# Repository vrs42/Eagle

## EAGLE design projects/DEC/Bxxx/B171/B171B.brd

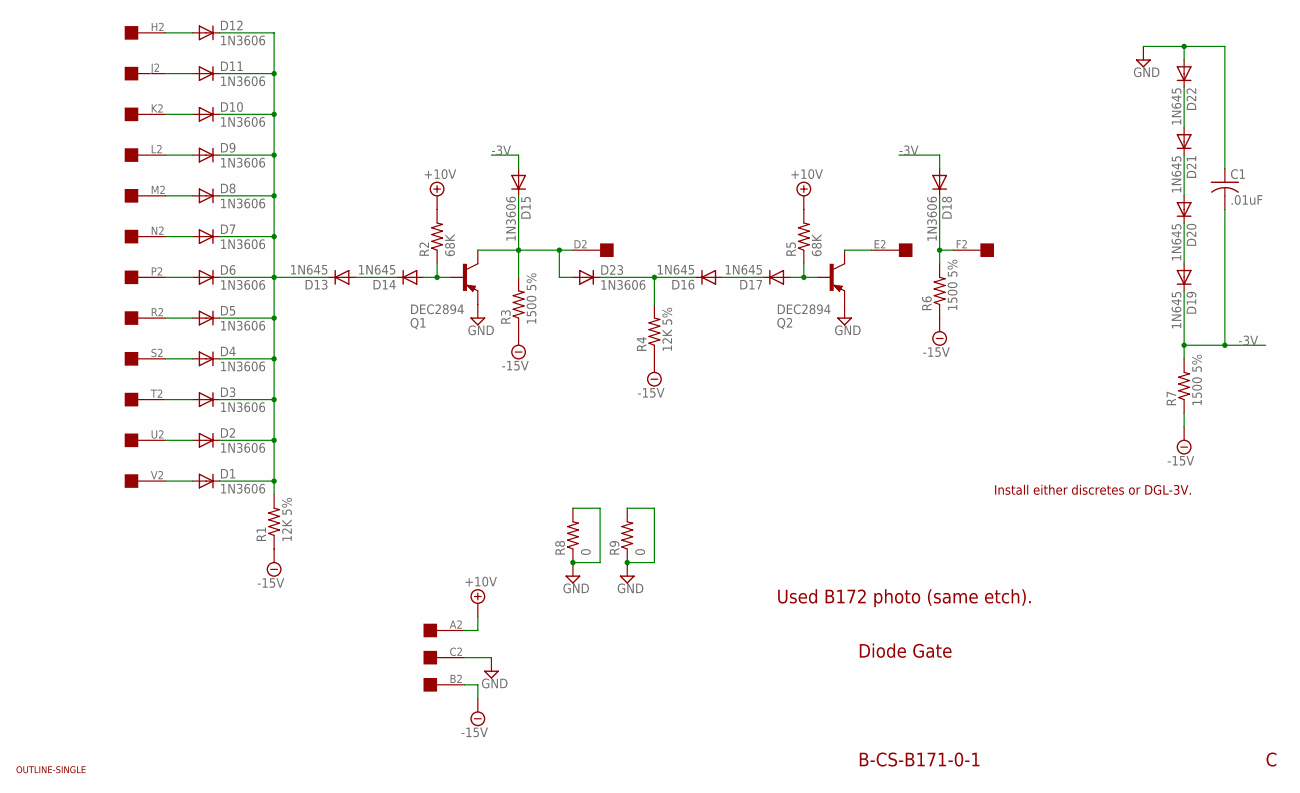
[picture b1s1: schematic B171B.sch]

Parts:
C1: .01uF; C063-025X075
D1, D2, D3, D4, D5, D6, D7, D8, D9, D10, D11, D12, D15, D18, D23: 1N3606; DO35-10
D13, D14, D16, D17, D19, D20, D21, D22: 1N645; DO35-10
Q1, Q2: DEC2894; TO5
R1, R4: 12K 5%; 0207/10
R2, R5: 68K; 0207/10
R3, R6, R7: 1500 5%; 0207/10
R8, R9: 0; 0207/10
U$1: OUTLINE-SINGLE; SINGLE
U$2: EDGE-1; EDGE-CON1

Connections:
+10V: R2.2, R5.2, U$2.A2
-3V: C1.2, D15.A, D18.A, D19.C, R7.2
-15V: R1.1, R3.1, R4.1, R6.1, R7.1, U$2.B2
D: D15.C, D23.A, Q1.3 (C), R3.2, U$2.D2
E: Q2.3 (C), U$2.E2
GND: C1.1, D22.A, Q1.1 (E), Q2.1 (E), R8.1, R8.2, R9.1, R9.2, U$2.C2
H: D12.A, U$2.H2
J: D11.A, U$2.J2
K: D10.A, U$2.K2
L: D9.A, U$2.L2
M: D8.A, U$2.M2
N: D7.A, U$2.N2
unnamed: D1.C, D2.C, D3.C, D4.C, D5.C, D6.C, D7.C, D8.C, D9.C, D10.C, D11.C, D12.C, D13.C, R1.2
unnamed: D13.A, D14.C
unnamed: D14.A, Q1.2 (B), R2.1
unnamed: D16.C, D23.C, R4.2
unnamed: D16.A, D17.C
unnamed: D17.A, Q2.2 (B), R5.1
unnamed: D18.C, R6.2, U$2.F2
unnamed: D19.A, D20.C
unnamed: D20.A, D21.C
unnamed: D21.A, D22.C
P: D6.A, U$2.P2
R: D5.A, U$2.R2
S: D4.A, U$2.S2
T: D3.A, U$2.T2
U: D2.A, U$2.U2
V: D1.A, U$2.V2

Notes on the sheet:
Diode Gate
B-CS-B171-0-1
Used B172 photo (same etch).
Install either discretes or DGL-3V.

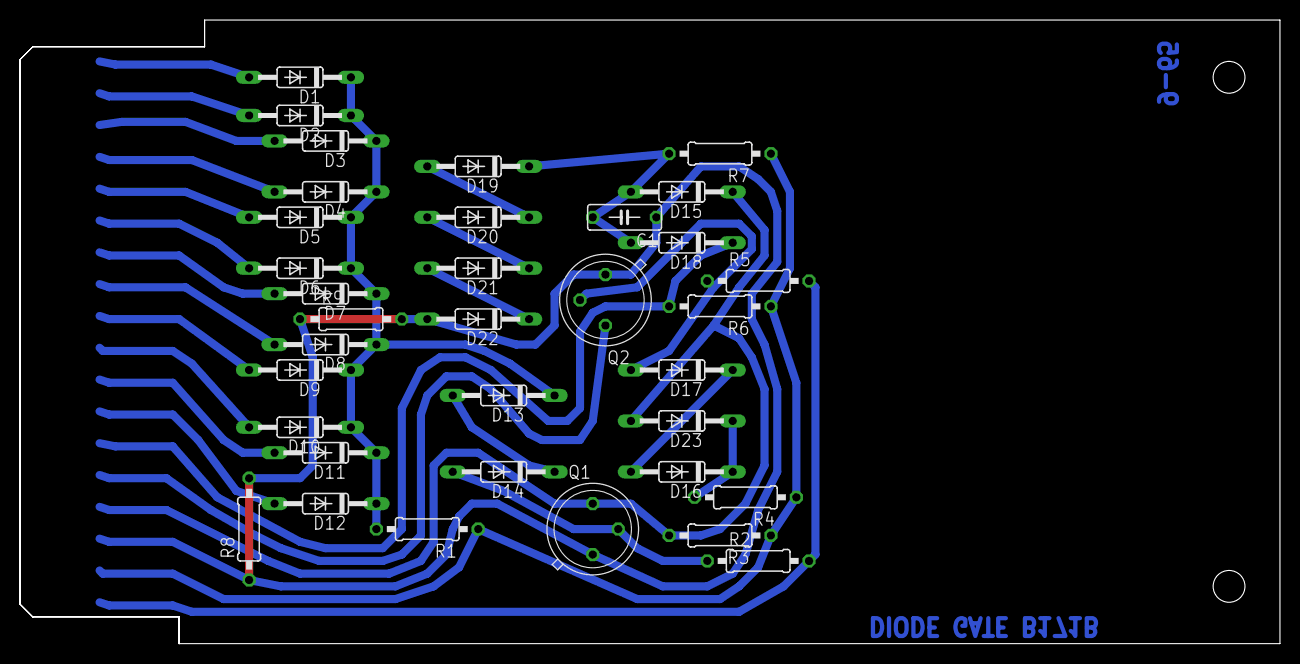
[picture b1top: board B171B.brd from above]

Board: 2 copper layers, 125.7 x 62.2 mm, 37 parts (0 on the bottom side), 28 nets.

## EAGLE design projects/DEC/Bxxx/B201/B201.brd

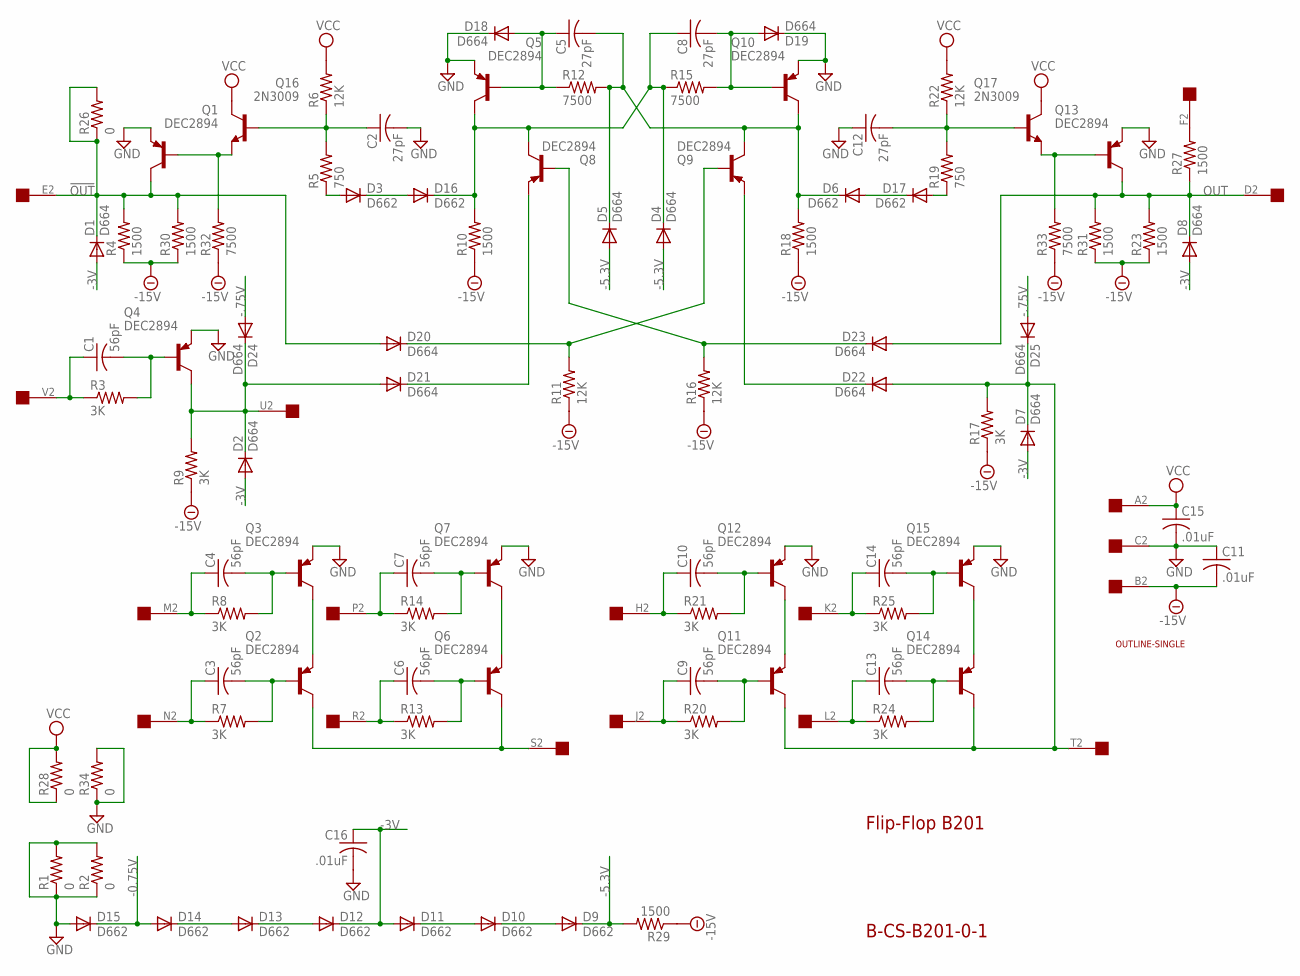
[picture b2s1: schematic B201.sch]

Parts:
C1, C3, C4, C6, C7, C9, C10, C13, C14: 56pF; C063-025X075
C2, C5, C8, C12: 27pF; C063-025X075
C11, C15, C16: .01uF; C063-025X075
D1, D2, D4, D5, D7, D8, D18, D19, D20, D21, D22, D23, D24, D25: D664; DO35-10
D3, D6, D9, D10, D11, D12, D13, D14, D15, D16, D17: D662; DO35-10
Q1, Q2, Q3, Q4, Q5, Q6, Q7, Q8, Q9, Q10, Q11, Q12, Q13, Q14, Q15: DEC2894; TO5
Q16, Q17: 2N3009; TO5
R1, R2, R26, R28, R34: 0; 0207/10
R3, R7, R8, R9, R13, R14, R17, R20, R21, R24, R25: 3K; 0207/10
R4, R10, R18, R23, R27, R29, R30, R31: 1500; 0207/10
R5, R19: 750; 0207/10
R6, R11, R16, R22: 12K; 0207/10
R12, R15, R32, R33: 7500; 0207/10
U$1: OUTLINE-SINGLE; SINGLE
U$2: EDGE-1; EDGE-CON1

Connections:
!OUT: D1.C, D20.A, Q1.3 (C), R4.2, R26.1, R26.2, R30.2, U$2.E2
-0.75V: D14.A, D15.C
-3V: C16.1, D1.A, D2.A, D7.A, D8.A, D11.A, D12.C
-5.3V: D4.A, D5.A, D9.C, R29.2
-15V: C11.2, R4.1, R9.1, R10.1, R11.1, R16.1, R17.1, R18.1, R23.1, R29.1, R30.1, R31.1, R32.1, R33.1, U$2.B2
-.75V: D24.A, D25.A
GND: C2.2, C11.1, C12.1, C15.2, C16.2, D15.A, D18.C, D19.C, Q1.1 (E), Q3.1 (E), Q4.1 (E), Q5.1 (E), Q7.1 (E), Q10.1 (E), Q12.1 (E), Q13.1 (E), Q15.1 (E), R1.1, R1.2, R2.1, R2.2, R34.1, R34.2, U$2.C2
unnamed: C4.1, R8.1, U$2.M2
unnamed: C4.2, Q3.2 (B), R8.2
unnamed: C3.1, R7.1, U$2.N2
unnamed: C3.2, Q2.2 (B), R7.2
unnamed: Q2.1 (E), Q3.3 (C)
unnamed: Q2.3 (C), Q6.3 (C), U$2.S2
unnamed: C7.1, R14.1, U$2.P2
unnamed: C7.2, Q7.2 (B), R14.2
unnamed: C6.1, R13.1, U$2.R2
unnamed: C6.2, Q6.2 (B), R13.2
unnamed: Q6.1 (E), Q7.3 (C)
unnamed: C1.1, R3.1, U$2.V2
unnamed: C10.1, R21.1, U$2.H2
unnamed: C10.2, Q12.2 (B), R21.2
unnamed: C9.1, R20.1, U$2.J2
unnamed: C9.2, Q11.2 (B), R20.2
unnamed: Q11.1 (E), Q12.3 (C)
unnamed: D7.C, D22.A, D25.C, Q11.3 (C), Q14.3 (C), R17.2, U$2.T2
unnamed: C14.1, R25.1, U$2.K2
unnamed: C14.2, Q15.2 (B), R25.2
unnamed: C13.1, R24.1, U$2.L2
unnamed: C13.2, Q14.2 (B), R24.2
unnamed: Q14.1 (E), Q15.3 (C)
unnamed: C1.2, Q4.2 (B), R3.2
unnamed: R27.2, U$2.F2
unnamed: D2.C, D21.A, D24.C, Q4.3 (C), R9.2, U$2.U2
unnamed: Q1.2 (B), Q16.1 (E), R32.2
unnamed: D9.A, D10.C
unnamed: D10.A, D11.C
unnamed: C2.1, Q16.2 (B), R5.2, R6.1
unnamed: D13.A, D14.C
unnamed: D12.A, D13.C
unnamed: D3.A, R5.1
unnamed: D3.C, D16.A
unnamed: C8.1, D4.C, D16.C, Q5.3 (C), Q8.3 (C), R10.2, R15.1
unnamed: D23.C, Q8.2 (B), R16.2
unnamed: C5.1, D18.A, Q5.2 (B), R12.1
unnamed: C5.2, D5.C, D6.C, Q9.3 (C), Q10.3 (C), R12.2, R18.2
unnamed: D20.C, Q9.2 (B), R11.2
unnamed: C8.2, D19.A, Q10.2 (B), R15.2
unnamed: D22.C, Q9.1 (E)
unnamed: D6.A, D17.C
unnamed: C12.2, Q17.2 (B), R19.2, R22.1
unnamed: D17.A, R19.1
unnamed: Q13.2 (B), Q17.1 (E), R33.2
unnamed: D21.C, Q8.1 (E)
OUT: D8.C, D23.A, Q13.3 (C), R23.2, R27.1, R31.2, U$2.D2
VCC: C15.1, Q16.3 (C), Q17.3 (C), R6.2, R22.2, R28.1, R28.2, U$2.A2

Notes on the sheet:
Flip-Flop B201
B-CS-B201-0-1

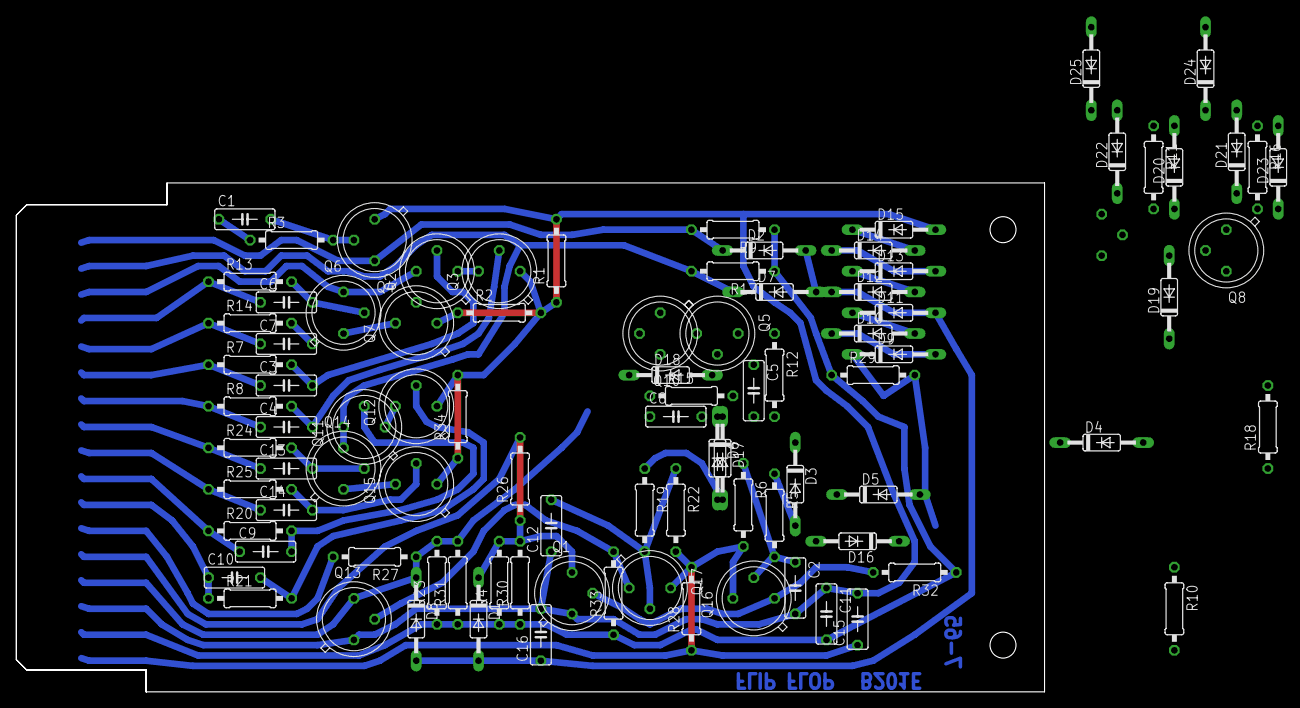
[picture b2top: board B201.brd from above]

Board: 2 copper layers, 125.7 x 62.2 mm, 94 parts (1 on the bottom side), 55 nets.
